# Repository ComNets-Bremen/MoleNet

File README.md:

# MoleNet: A Wireless Underground Sensor Network Platform

**MoleNet** is a versatile Wireless Underground Sensor Network (WUSN) platform designed for education and low-power environmental monitoring.
This repository contains all relevant resources, including PCB layouts, source code, and examples to test and evaluate the platform.

Further information can be found on the official [MoleNet Website](https://molenet.org/)!

> ⚠️ **Note:** This is an active project. The files and directory structure are subject to change.

## New ESP32-based MoleNet!

After a long journey, we are finally at a point where we are testing the current version on a larger scale.
The latest version of MoleNet features several key improvements:

- **ESP32-S3 microcontroller**: A powerful yet energy-efficient processor that supports various development ecosystems including [MicroPython](https://micropython.org/), [Arduino](https://www.arduino.cc/), and [RiotOS](https://www.riot-os.org/)
- **SDI-12 sensor interface**: Compatible with high-quality environmental sensors
- **Micro-SD card support**: Enables extensive local data storage
- **SX1276-based LoRa transceiver**: Provides long-range wireless communication
- **On-board BME280 sensor**: Measures temperature, barometric pressure, and humidity [BME280](https://www.bosch-sensortec.com/products/environmental-sensors/humidity-sensors-bme280/)
- **Low-power design**: Ensures long battery life for extended deployments
- **qwiic connectivity**: Simplifies integration of I2C-based sensors, as, for
  example, available here: [Sparkfun](https://www.sparkfun.com/qwiic)

## Documentation

New users can start with the **[Getting Started Guide](doc/GETTING_STARTED.md)** to identify their board version and find the correct software, hardware documentation, and setup instructions.

The main documentation of MoleNet is available [here in the doc directory](doc). There, you can also find the **[FAQ](doc/FAQ.md)**.

## Older Versions of MoleNet (pre-ESP)

In the past decade, we used and evaluated different microcontroller platforms
for MoleNet. The documentation can be found in the corresponding directories:

- [For ATMEGA-based boards](doc/ATMEGA)
- [For the STM32-based boards (STM32F411)](doc/stm32)

## Changelog

The list of changes and the evolution of MoleNet is listed in the
[changelog](CHANGELOG.md).

## Publications

The following list gives some MoleNet-related publications:

- Gellhaar, M., Dede, J., Koehler, H., & Förster, A. (2016, February). Design and Evaluation of Underground Wireless Sensor Networks for Reforestation Monitoring. [In EWSN (pp. 229-230)](https://dl.acm.org/doi/10.5555/2893711.2893747).
- Zaman, I., Dede, J., Gellhaar, M., Koehler, H., & Foerster, A. (2016). Molenet: A new sensor node for underground monitoring. [IEEE SenseApp](https://www.researchgate.net/publication/309397324_MoleNet_A_New_Sensor_Node_for_Underground_Monitoring).
- Zaman, I., Gellhaar, M., Dede, J., Koehler, H., & Foerster, A. (2016, November). Design and evaluation of MoleNet for wireless underground sensor networks. In 2016 IEEE 41st conference on local computer networks workshops (LCN workshops) (pp. 145-147), [2016 IEEE 41st Conference on Local Computer Networks Workshops (LCN Workshops), Dubai, United Arab Emirates, 2016, pp. 145-147](https://doi.org/10.1109/LCN.2016.040).
- Dede, J., Helms, D., & Förster, A. (2021). MoleNet: An Underground Sensor Network for Soil Monitoring. [Electronic Communications of the EASST, 80](https://doi.org/10.14279/tuj.eceasst.80.1132)
- Sambo, D. W., Dede, J., Mitton, N., & Förster, A. (2023). FuzDeMa: A portable Fuzzy-based Decision-Making tool for reliable communication in Wireless Underground Sensor Networks. [ITU Journal on Future and Evolving Technologies, 4(3), 419-433](https://www.doi.org/10.52953/IXIP2995).
- Block, J., Könsgen, A., Dede, J., Förster, A. (2026, January). Precise Low-Current Measurement Techniques for IoT Devices: A Case Study on MoleNet. [arxiv, Electrical Engineering and Systems Science > Signal Processing](https://doi.org/10.48550/arXiv.2601.16727)

## I need Support or want to Contribute!

The development of MoleNet is mainly done on GitHub. You have the following
channels:

- For discussions, we are currently trying to move from our mailing list to [GitHub discussions](https://github.com/ComNets-Bremen/MoleNet/discussions). Feel free to join and open new discussions directly [here](https://github.com/ComNets-Bremen/MoleNet/discussions)!
- You found an issue? [Open an Issue on GitHub](https://github.com/ComNets-Bremen/MoleNet/issues)!
- You already have a solution? Perfect! Feel free to [create a Pull request on GitHub](https://github.com/ComNets-Bremen/MoleNet/pulls)!

If you need support with the git fundamentals like cloning, forking, branching,
the different copies of the code etc., please refer to the [GitHub
documentation](https://docs.github.com).

## I want to have MoleNet!

MoleNet is a dynamic project that is constantly evolving. At its current stage, we do not offer a ready-to-use, fully certified product with complete end-user support.

If you would like to contribute to the development of MoleNet and need hardware for testing and further development, you have two options:

1. **Build the hardware yourself.** All the necessary resources can be found in this repository.
2. **Order evaluation boards** from our partner [Intergalactic Circuits](https://intergalactic-circuits.de) for personal use.

## Contributors

Many students and researchers contribute to the MoleNet project.
See the full list of contributors in [CONTRIBUTORS.md](CONTRIBUTORS.md).

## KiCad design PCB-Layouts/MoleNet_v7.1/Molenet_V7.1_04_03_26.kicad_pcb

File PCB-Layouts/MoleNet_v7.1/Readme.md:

This folder contain Kicad files of Molenet V7.1 Board.

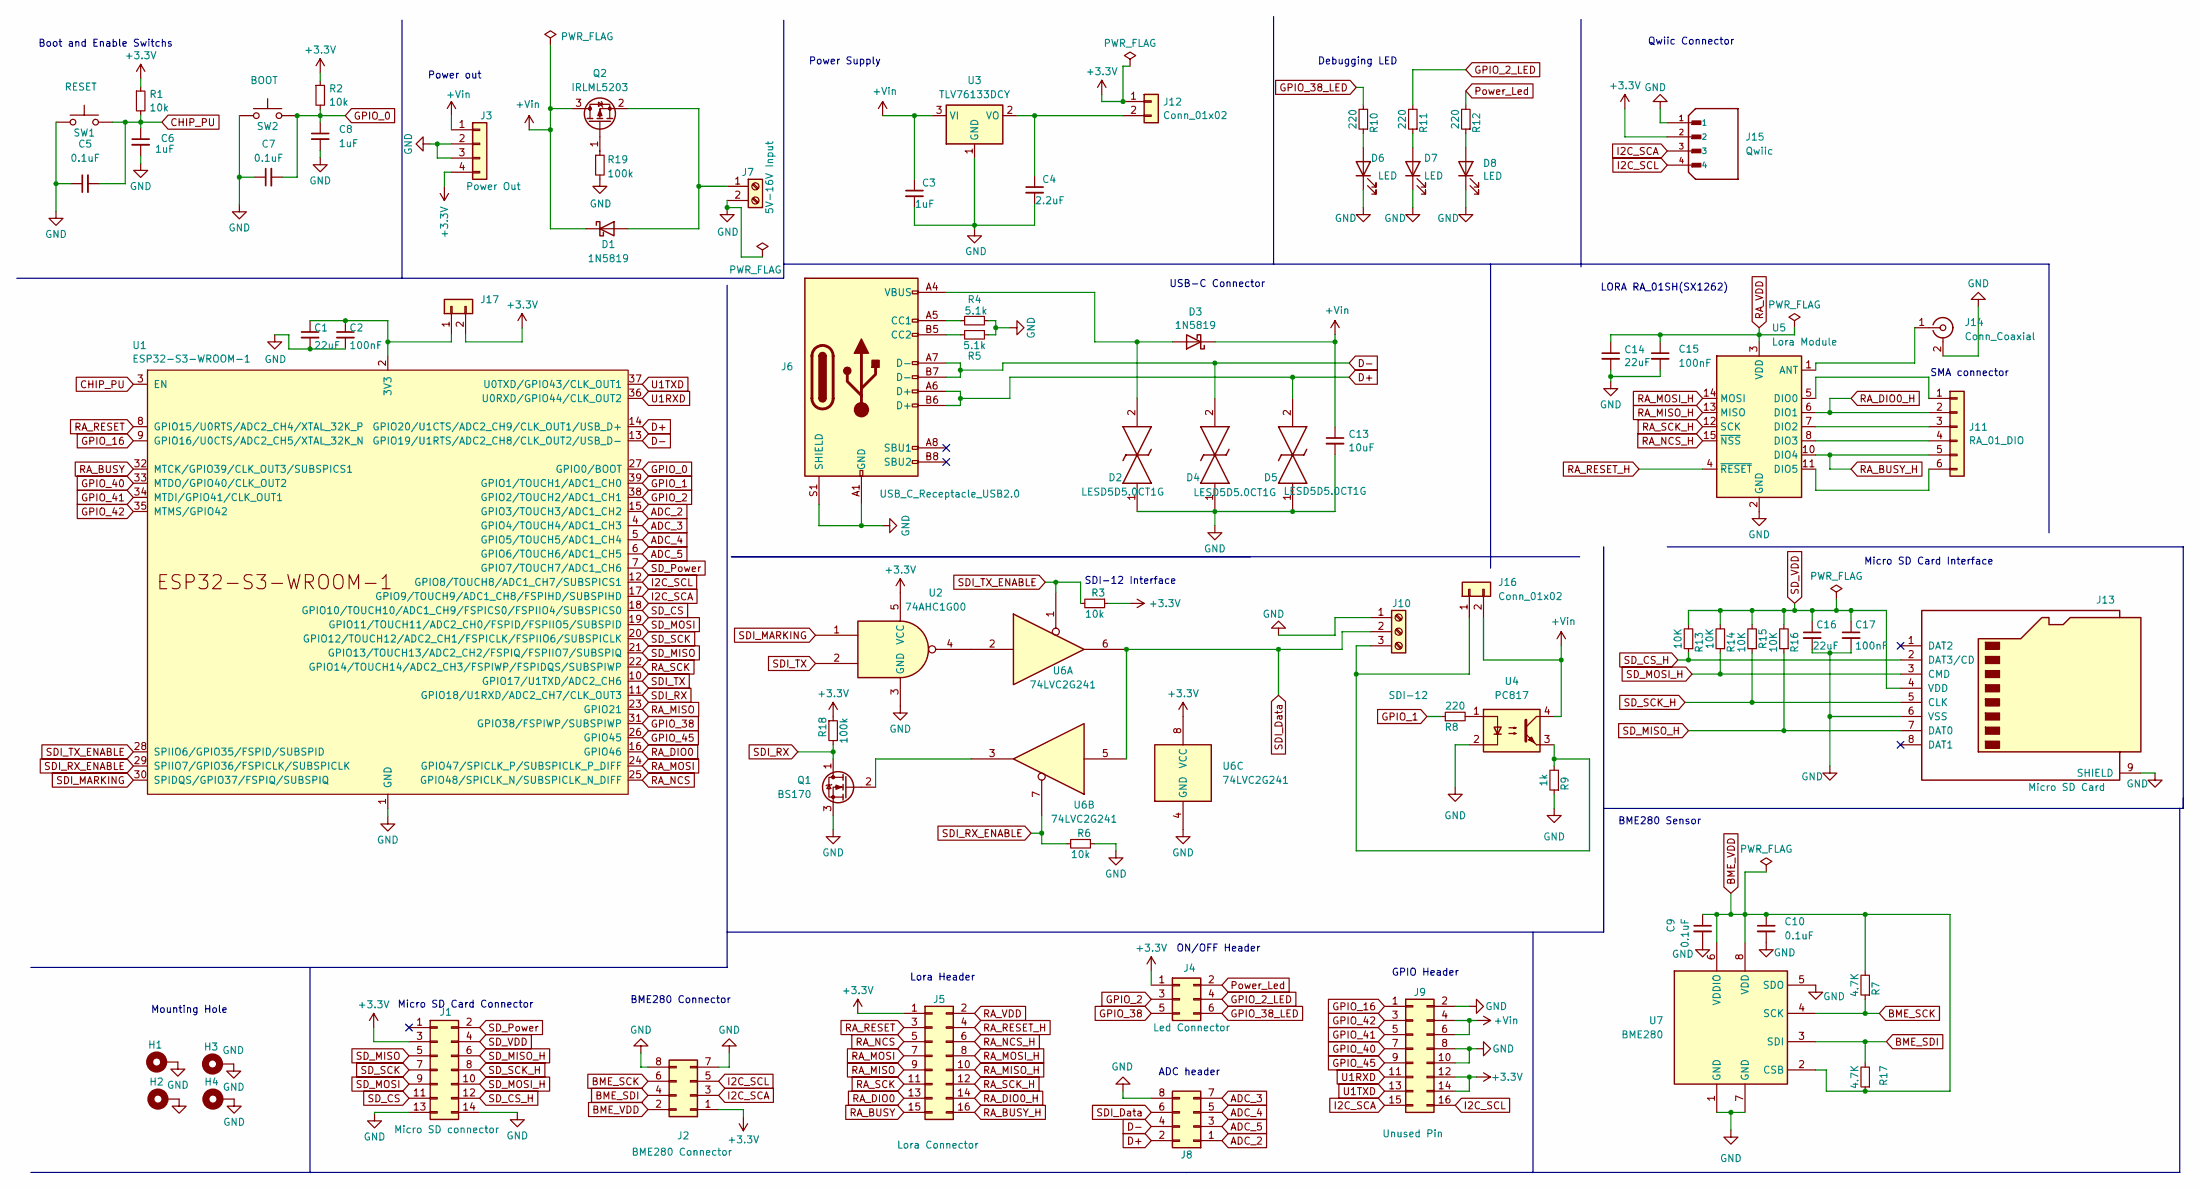
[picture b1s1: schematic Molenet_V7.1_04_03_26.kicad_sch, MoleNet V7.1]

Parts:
C1, C14: 22uF; C_0805_2012Metric_Pad1.18x1.45mm_HandSolder
C2, C15: 100nF; C_0805_2012Metric_Pad1.18x1.45mm_HandSolder
C3, C6, C8: 1uF; C_0805_2012Metric_Pad1.18x1.45mm_HandSolder
C4: 2.2uF; C_0805_2012Metric_Pad1.18x1.45mm_HandSolder
C5, C7, C9, C10: 0.1uF; C_0805_2012Metric_Pad1.18x1.45mm_HandSolder
C13: 10uF; C_0805_2012Metric_Pad1.18x1.45mm_HandSolder
C16: 22uF; C_0402_1005Metric_Pad0.74x0.62mm_HandSolder
C17: 100nF; C_0402_1005Metric_Pad0.74x0.62mm_HandSolder
D1, D3: 1N5819; D_DO-41_SOD81_P10.16mm_Horizontal
D2, D4, D5: LESD5D5.0CT1G; LESD5D50CT1G; Manufacturer_Part_Number LESD5D5.0CT1G; JLC PART C383211
D6, D7, D8: LED; LED_0805_2012Metric_Pad1.15x1.40mm_HandSolder
H1, H2, H3, H4: MountingHole_Pad; MountingHole_3.2mm_M3_Pad
J1: Micro SD connector; PinHeader_2x07_P2.54mm_Vertical
J2: BME280 Connector; PinHeader_2x04_P2.54mm_Vertical
J3: Power Out; PinHeader_1x04_P2.54mm_Vertical
J4: Led Connector; PinHeader_2x03_P2.54mm_Vertical
J5: Lora Connector; PinHeader_2x08_P2.54mm_Vertical
J6: USB_C_Receptacle_USB2.0; USB_C_Receptacle_G-Switch_GT-USB-7010ASV; JLC PART C2936185
J7: 5V-16V Input; TerminalBlock_Phoenix_PT-1,5-2-3.5-H_1x02_P3.50mm_Horizontal; JLC PART C89122
J8: PinHeader_2x04_P2.54mm_Vertical
J9: Unused Pin; PinHeader_2x08_P2.54mm_Vertical
J10: SDI-12; TerminalBlock_Phoenix_PT-1,5-3-3.5-H_1x03_P3.50mm_Horizontal; JLC PART C91152
J11: RA_01_DIO; PinHeader_1x06_P2.54mm_Vertical
J12, J16, J17: Conn_01x02; PinHeader_1x02_P2.54mm_Vertical
J13: Micro SD Card; microSD_HC_Molex_104031-0811; JLC PART C428492
J14: Conn_Coaxial; SMA_Amphenol_901-143_Horizontal; JLC PART C914554
J15: Qwiic; SPARKFUN_PRT-14417; PARTREV NA
Q1: BS170; TO-92_Inline
Q2: IRLML5203; SOT-23
R1, R2, R3, R6: 10k; R_0805_2012Metric_Pad1.20x1.40mm_HandSolder
R4, R5: 5.1k; R_0402_1005Metric_Pad0.72x0.64mm_HandSolder
R7, R17: 4.7K; R_0402_1005Metric_Pad0.72x0.64mm_HandSolder
R8, R10, R11, R12: 220; R_0805_2012Metric_Pad1.20x1.40mm_HandSolder
R9: 1k; R_0805_2012Metric_Pad1.20x1.40mm_HandSolder
R13, R14, R15, R16: 10K; R_0402_1005Metric_Pad0.72x0.64mm_HandSolder
R18, R19: 100k; R_0805_2012Metric_Pad1.20x1.40mm_HandSolder
SW1: RESET; SW_PUSH_6mm_H4.3mm; JLC PART C273464
SW2: BOOT; SW_PUSH_6mm_H4.3mm; JLC PART C273464
U1: ESP32-S3-WROOM-1; JLC PART C2913198
U2: 74AHC1G00; SC-74A-5_1.55x2.9mm_P0.95mm
U3: TLV76133DCY; SOT-223-3_TabPin2
U4: PC817; DIP-4_W7.62mm
U5: Lora Module; Ai-Thinker-Ra-01-LoRa
U6: 74LVC2G241; SOP65P400X130-8N
U7: BME280; Bosch_LGA-8_2.5x2.5mm_P0.65mm_ClockwisePinNumbering

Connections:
+3.3V: J1.3, J2.1, J3.4, J4.1, J5.1, J9.12, J9.14, J12.1, J15.2, J17.2, R1.1, R2.1, R3.1, R18.1, U2.5 (VCC), U6.8 (VCC)
+Vin: C3.1, C13.1, D1.1 (K), D3.1 (K), J3.1, J9.4, J9.6, J16.2, Q2.3 (D), U3.3 (VI), U4.4
ADC_2: J8.1, U1.15 (GPIO3/TOUCH3/ADC1_CH2)
ADC_3: J8.7 (Pin_4), U1.4 (GPIO4/TOUCH4/ADC1_CH3)
ADC_4: J8.5 (Pin_3), U1.5 (GPIO5/TOUCH5/ADC1_CH4)
ADC_5: J8.3 (Pin_2), U1.6 (GPIO6/TOUCH6/ADC1_CH5)
BME_SCK: J2.6 (Pin_7), R7.1, U7.4 (SCK)
BME_SDI: J2.4 (Pin_6), R17.2, U7.3 (SDI)
BME_VDD: C9.1, C10.1, J2.2 (Pin_5), R7.2, R17.1, U7.2 (CSB), U7.6 (VDDIO), U7.8 (VDD)
CHIP_PU: C5.2, C6.1, R1.2, SW1.2, U1.3 (EN)
D+: D5.2, J6.A6 (D+), J6.B6 (D+), J8.2 (Pin_5), U1.14 (GPIO20/U1CTS/ADC2_CH9/CLK_OUT1/USB_D+)
D-: D4.2, J6.A7 (D-), J6.B7 (D-), J8.4 (Pin_6), U1.13 (GPIO19/U1RTS/ADC2_CH8/CLK_OUT2/USB_D-)
GND: C1.2, C2.2, C3.2, C4.2, C5.1, C6.2, C7.1, C8.2, C9.2, C10.2, C13.2, C14.2, C15.2, C16.2, C17.2, D2.1, D4.1, D5.1, D6.1 (K), D7.1 (K), D8.1 (K), H1.1, H2.1, H3.1, H4.1, J1.13, J1.14, J2.7 (Pin_4), J2.8, J3.2, J3.3, J6.A1 (GND), J6.A12 (GND), J6.B1 (GND), J6.B12 (GND), J6.S1 (SHIELD), J7.2, J8.8, J9.2, J9.8, J9.10, J10.1, J13.6 (VSS), J13.9 (SHIELD), J14.2 (Ext), J15.1, Q1.3 (S), R4.1, R5.1, R6.1, R9.1, R19.2, SW1.1, SW2.1, U1.1 (GND), U1.40 (GND), U1.41 (GND), U2.3 (GND), U3.1 (GND), U4.2, U5.2 (GND), U5.9 (GND), U5.16 (GND), U6.4 (GND), U7.1 (GND), U7.5 (SDO), U7.7 (GND)
GPIO_0: C7.2, C8.1, R2.2, SW2.2, U1.27 (GPIO0/BOOT)
GPIO_1: R8.1, U1.39 (GPIO1/TOUCH1/ADC1_CH0)
GPIO_2: J4.3 (Pin_2), U1.38 (GPIO2/TOUCH2/ADC1_CH1)
GPIO_2_LED: J4.4 (Pin_5), R11.2
GPIO_16: J9.1, U1.9 (GPIO16/U0CTS/ADC2_CH5/XTAL_32K_N)
GPIO_38: J4.5 (Pin_3), U1.31 (GPIO38/FSPIWP/SUBSPIWP)
GPIO_38_LED: J4.6, R10.2
GPIO_40: J9.7, U1.33 (MTDO/GPIO40/CLK_OUT2)
GPIO_41: J9.5, U1.34 (MTDI/GPIO41/CLK_OUT1)
GPIO_42: J9.3, U1.35 (MTMS/GPIO42)
GPIO_45: J9.9, U1.26 (GPIO45)
I2C_SCA: J2.3 (Pin_2), J9.15, J15.3, U1.17 (GPIO9/TOUCH9/ADC1_CH8/FSPIHD/SUBSPIHD)
I2C_SCL: J2.5 (Pin_3), J9.16, J15.4, U1.12 (GPIO8/TOUCH8/ADC1_CH7/SUBSPICS1)
unnamed: D1.2 (A), J7.1, Q2.2 (S)
unnamed: D2.2, D3.2 (A), J6.A4 (VBUS), J6.A9 (VBUS), J6.B4 (VBUS), J6.B9 (VBUS)
unnamed: D6.2 (A), R10.1
unnamed: D7.2 (A), R11.1
unnamed: D8.2 (A), R12.1
unnamed: J6.A5 (CC1), R4.2
unnamed: J6.B5 (CC2), R5.2
unnamed: J10.3, J16.1, R9.2, U4.3
unnamed: J11.1, U5.5 (DIO0)
unnamed: J11.3, U5.7 (DIO2)
unnamed: J11.4, U5.8 (DIO3)
unnamed: J11.6, U5.11 (DIO5)
unnamed: C4.1, J12.2, U3.2 (VO)
unnamed: J14.1 (In), U5.1 (ANT)
unnamed: C1.1, C2.1, J17.1, U1.2 (3V3)
unnamed: Q1.2 (G), U6.3
unnamed: Q2.1 (G), R19.1
unnamed: R8.2, U4.1
unnamed: U2.4, U6.2
Power_Led: J4.2 (Pin_4), R12.2
RA_BUSY: J5.15, U1.32 (MTCK/GPIO39/CLK_OUT3/SUBSPICS1)
RA_BUSY_H: J5.16, J11.5, U5.10 (DIO4)
RA_DIO0: J5.13, U1.16 (GPIO46)
RA_DIO0_H: J5.14, J11.2, U5.6 (DIO1)
RA_MISO: J5.9, U1.23 (GPIO21)
RA_MISO_H: J5.10, U5.13 (MISO)
RA_MOSI: J5.7, U1.24 (GPIO47/SPICLK_P/SUBSPICLK_P_DIFF)
RA_MOSI_H: J5.8, U5.14 (MOSI)
RA_NCS: J5.5, U1.25 (GPIO48/SPICLK_N/SUBSPICLK_N_DIFF)
RA_NCS_H: J5.6, U5.15 (~NSS)
RA_RESET: J5.3, U1.8 (GPIO15/U0RTS/ADC2_CH4/XTAL_32K_P)
RA_RESET_H: J5.4, U5.4 (~RESET)
RA_SCK: J5.11, U1.22 (GPIO14/TOUCH14/ADC2_CH3/FSPIWP/FSPIDQS/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)
RA_SCK_H: J5.12, U5.12 (SCK)
RA_VDD: C14.1, C15.1, J5.2, U5.3 (VDD)
SDI_Data: J8.6 (Pin_7), J10.2, U6.5, U6.6
SDI_MARKING: U1.30 (SPIDQS/GPIO37/FSPIQ/SUBSPIQ), U2.1
SDI_RX: Q1.1 (D), R18.2, U1.11 (GPIO18/U1RXD/ADC2_CH7/CLK_OUT3)
SDI_RX_ENABLE: R6.2, U1.29 (SPIIO7/GPIO36/FSPICLK/SUBSPICLK), U6.7
SDI_TX: U1.10 (GPIO17/U1TXD/ADC2_CH6), U2.2
SDI_TX_ENABLE: R3.2, U1.28 (SPIIO6/GPIO35/FSPID/SUBSPID), U6.1
SD_CS: J1.11, U1.18 (GPIO10/TOUCH10/ADC1_CH9/FSPICS0/FSPIIO4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)
SD_CS_H: J1.12, J13.2 (DAT3/CD), R13.1
SD_MISO: J1.5, U1.21 (GPIO13/TOUCH13/ADC2_CH2/FSPIQ/FSPIIO7/S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)
SD_MISO_H: J1.6, J13.7 (DAT0), R16.1
SD_MOSI: J1.9, U1.19 (GPIO11/TOUCH11/ADC2_CH0/FSPID/FSPIIO5/S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)
SD_MOSI_H: J1.10, J13.3 (CMD), R14.1
SD_Power: J1.2, U1.7 (GPIO7/TOUCH7/ADC1_CH6)
SD_SCK: J1.7, U1.20 (GPIO12/TOUCH12/ADC2_CH1/FSPICLK/FSPIIO6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)
SD_SCK_H: J1.8, J13.5 (CLK), R15.1
SD_VDD: C16.1, C17.1, J1.4, J13.4 (VDD), R13.2, R14.2, R15.2, R16.2
U1RXD: J9.11, U1.36 (U0RXD/GPIO44/CLK_OUT2)
U1TXD: J9.13, U1.37 (U0TXD/GPIO43/CLK_OUT1)

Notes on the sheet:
Lora Header
ON/OFF Header
Boot and Enable Switchs
SMA connector
Debugging LED
LORA RA_01SH(SX1262)
Power Supply
USB-C Connector
Power out
GPIO Header
Micro SD Card Connector
SDI-12 Interface
ADC header
BME280 Sensor
Qwiic Connector
Mounting Hole
BME280 Connector
Micro SD Card Interface

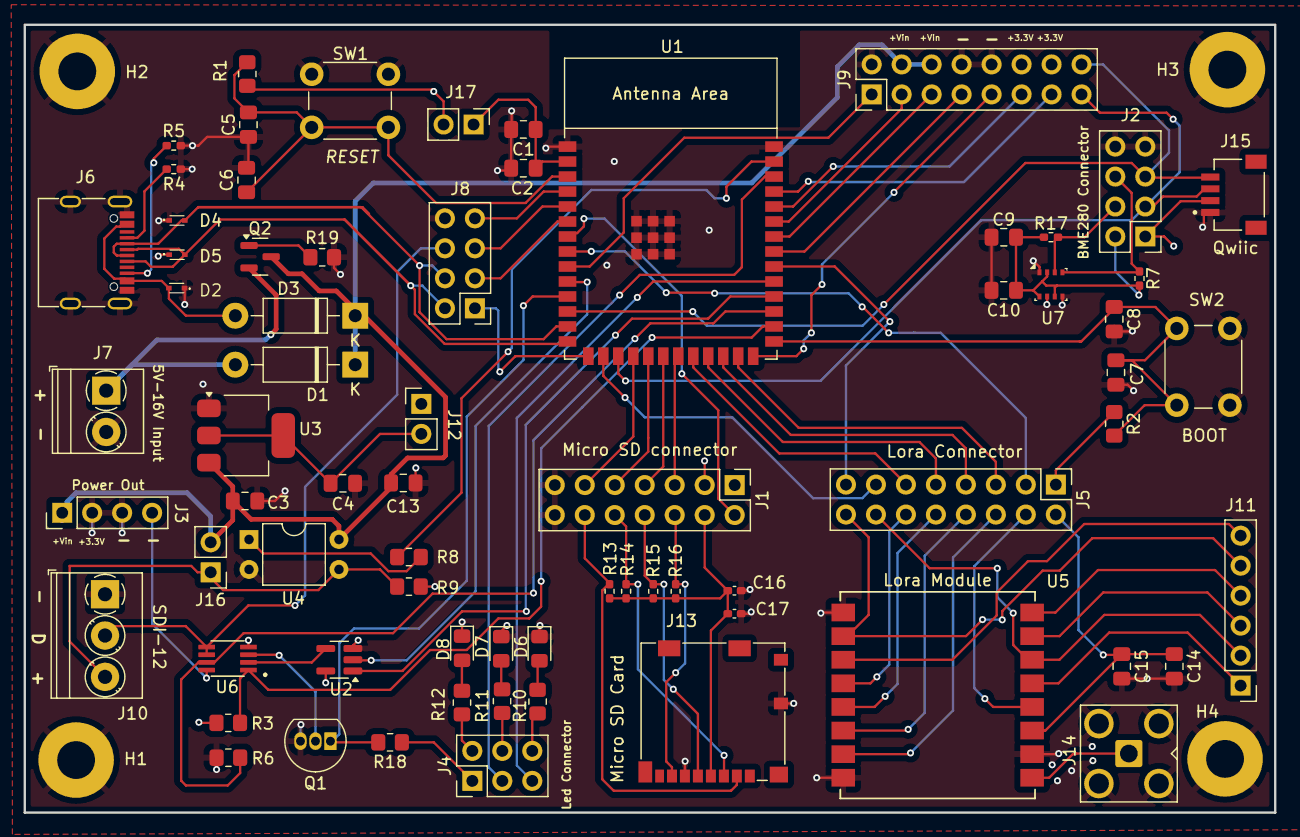
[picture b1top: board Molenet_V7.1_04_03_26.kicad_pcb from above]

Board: 4 copper layers, 106.0 x 66.8 mm, 75 parts (1 on the bottom side), 79 nets.

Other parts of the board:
G2: LOGO

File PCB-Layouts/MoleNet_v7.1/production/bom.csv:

Designator,Footprint,Quantity,Value,LCSC Part #
"C1, C14",0805,2,22uF,
"C10, C5, C7, C9",0805,4,0.1uF,
C13,0805,1,10uF,
"C15, C2",0805,2,100nF,
C16,0402,1,22uF,
C17,0402,1,100nF,
"C3, C6, C8",0805,3,1uF,
C4,0805,1,2.2uF,
"D1, D3",D_DO-41_SOD81_P10.16mm_Horizontal,2,1N5819,
"D2, D4, D5",LESD5D50CT1G,3,LESD5D5.0CT1G,
"D6, D7, D8",0805,3,LED,
"H1, H2, H3, H4",MountingHole_3.2mm_M3_Pad,4,MountingHole_Pad,
J1,PinHeader_2x07_P2.54mm_Vertical,1,Micro SD connector,
J10,"TerminalBlock_Phoenix_PT-1,5-3-3.5-H_1x03_P3.50mm_Horizontal",1,SDI-12,
J11,PinHeader_1x06_P2.54mm_Vertical,1,RA_01_DIO,
"J12, J16, J17",PinHeader_1x02_P2.54mm_Vertical,3,Conn_01x02,
J13,microSD_HC_Molex_104031-0811,1,Micro SD Card,
J14,SMA_Amphenol_901-143_Horizontal,1,Conn_Coaxial,
J15,SPARKFUN_PRT-14417,1,Qwiic,
J2,PinHeader_2x04_P2.54mm_Vertical,1,BME280 Connector,
J3,PinHeader_1x04_P2.54mm_Vertical,1,Power Out,
J4,PinHeader_2x03_P2.54mm_Vertical,1,Led Connector,
J5,PinHeader_2x08_P2.54mm_Vertical,1,Lora Connector,
J6,USB_C_Receptacle_G-Switch_GT-USB-7010ASV,1,USB_C_Receptacle_USB2.0,
J7,"TerminalBlock_Phoenix_PT-1,5-2-3.5-H_1x02_P3.50mm_Horizontal",1,5V-16V Input,
J8,PinHeader_2x04_P2.54mm_Vertical,1,~,
J9,PinHeader_2x08_P2.54mm_Vertical,1,Unused Pin,
Q1,TO-92_Inline,1,BS170,
Q2,SOT-23,1,IRLML5203,
"R1, R2, R3, R6",0805,4,10k,
"R10, R11, R12, R8",0805,4,220,
"R13, R14, R15, R16",0402,4,10K,
"R17, R7",0402,2,4.7K,
"R18, R19",0805,2,100k,
"R4, R5",0402,2,5.1k,
R9,0805,1,1k,
SW1,SW_PUSH_6mm_H4.3mm,1,RESET,
SW2,SW_PUSH_6mm_H4.3mm,1,BOOT,
U1,ESP32-S3-WROOM-1,1,ESP32-S3-WROOM-1,
U2,SC-74A-5_1.55x2.9mm_P0.95mm,1,74AHC1G00,
U3,SOT-223-3_TabPin2,1,TLV76133DCY,
U4,DIP-4_W7.62mm,1,PC817,
U5,Ai-Thinker-Ra-01-LoRa,1,Lora Module,
U6,SOP65P400X130-8N,1,74LVC2G241,
U7,Bosch_LGA-8_2.5x2.5mm_P0.65mm_ClockwisePinNumbering,1,BME280,

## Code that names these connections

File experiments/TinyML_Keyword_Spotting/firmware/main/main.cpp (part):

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// MOLeNET V7.1 + INMP441
// ============================================================
//
// SCK = GPIO40
// WS  = GPIO41
// SD  = GPIO42
//
// L/R = GND
//
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// MOLeNET V7.1 ONBOARD ACTION LED
// ============================================================
//
// D6 = GPIO38
//
// GPIO HIGH -> LED ON
// GPIO LOW  -> LED OFF
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
    ESP_LOGI(
        TAG,
        "Onboard action LED initialized on GPIO38 / D6"
    );
}

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    // STARTUP LED TEST
    // ========================================================
    //
    // D6 / GPIO38 should blink 5 times.
    //
    // THIS TELLS YOU EXACTLY WHICH PHYSICAL LED IS CONTROLLED.
    //
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
    ESP_LOGI(
        TAG,
        "Testing D6 / GPIO38 LED..."
    );


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
    ESP_LOGI(
        TAG,
        "D6 / GPIO38 LED test complete."
    );


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
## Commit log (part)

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2025-12-15 Move table with pins to separate directory
2025-12-15 Add 6.2 HW table
2025-12-15 Move the table with the parts to separate files
2025-12-15 Tidy up repo
2025-12-15 Updated changelog and Readme with new version
2025-12-15 More details about the older MoleNet versions
2025-12-16 Add support channels to the Readme!
2025-12-16 Add pins for MoleNet 7.0
2025-12-16 Minor format issues
2025-12-16 Add more links
2025-12-16 First draft of a FAQ
2025-12-16 Link doc and FAQ
2026-01-16 Simple test script for new 7.0 boards
2026-01-20 Explicity set frequency
2026-02-20 Add new publication
2026-02-20 typo
2026-02-20 Bump cryptography from 46.0.3 to 46.0.5 in /tools/MoleWarden/testApp_7.0
    Bumps [cryptography](https://github.com/pyca/cryptography) from 46.0.3 to 46.0.5.
    - [Changelog](https://github.com/pyca/cryptography/blob/main/CHANGELOG.rst)
    - [Commits](https://github.com/pyca/cryptography/compare/46.0.3...46.0.5)
    ---
    updated-dependencies:
    - dependency-name: cryptography
2026-02-27 clean up structure of LoRa test between different versions.
2026-02-27 gitignore for Mac OS.
2026-02-27 test V7 script debug
2026-03-05 rename dir
2026-03-05 Rename some experiment directories
2026-03-05 Add the code from the EWSN 2025
2026-03-05 Do not use the water sensor dir as a submodule
2026-03-05 Add fundamental information for MoleNet 7.1
2026-03-31 test script for version 7.1
2026-04-16 Add link to RA-01SH module on ai-thinker
2026-06-09 Information about the Bad Kissingen MoleNet distribution
2026-06-25 Add MoleNet v7.1 README
2026-06-25 Refactor README.md for MoleNet v7.1
    Updated README.md to improve formatting and clarity.
2026-06-25 Revise README for deep sleep test instructions
    Updated formatting and clarified instructions in README.
2026-06-25 Update README.md for LoRaWAN connection tests
2026-06-26 Update MoleNet v7.1 LoRaWAN Setup Guide
    Removed author information from the setup guide.
2026-06-26 Update LoRaWAN Setup documentation
    Removed instructions for unique TTN end device ID generation and example output.
2026-06-26 Refactor README.md for Markdown compliance
    Updated the README.md to use Markdown formatting and improved clarity.
2026-06-28 Power measurement and battery voltager reader software and documentation
